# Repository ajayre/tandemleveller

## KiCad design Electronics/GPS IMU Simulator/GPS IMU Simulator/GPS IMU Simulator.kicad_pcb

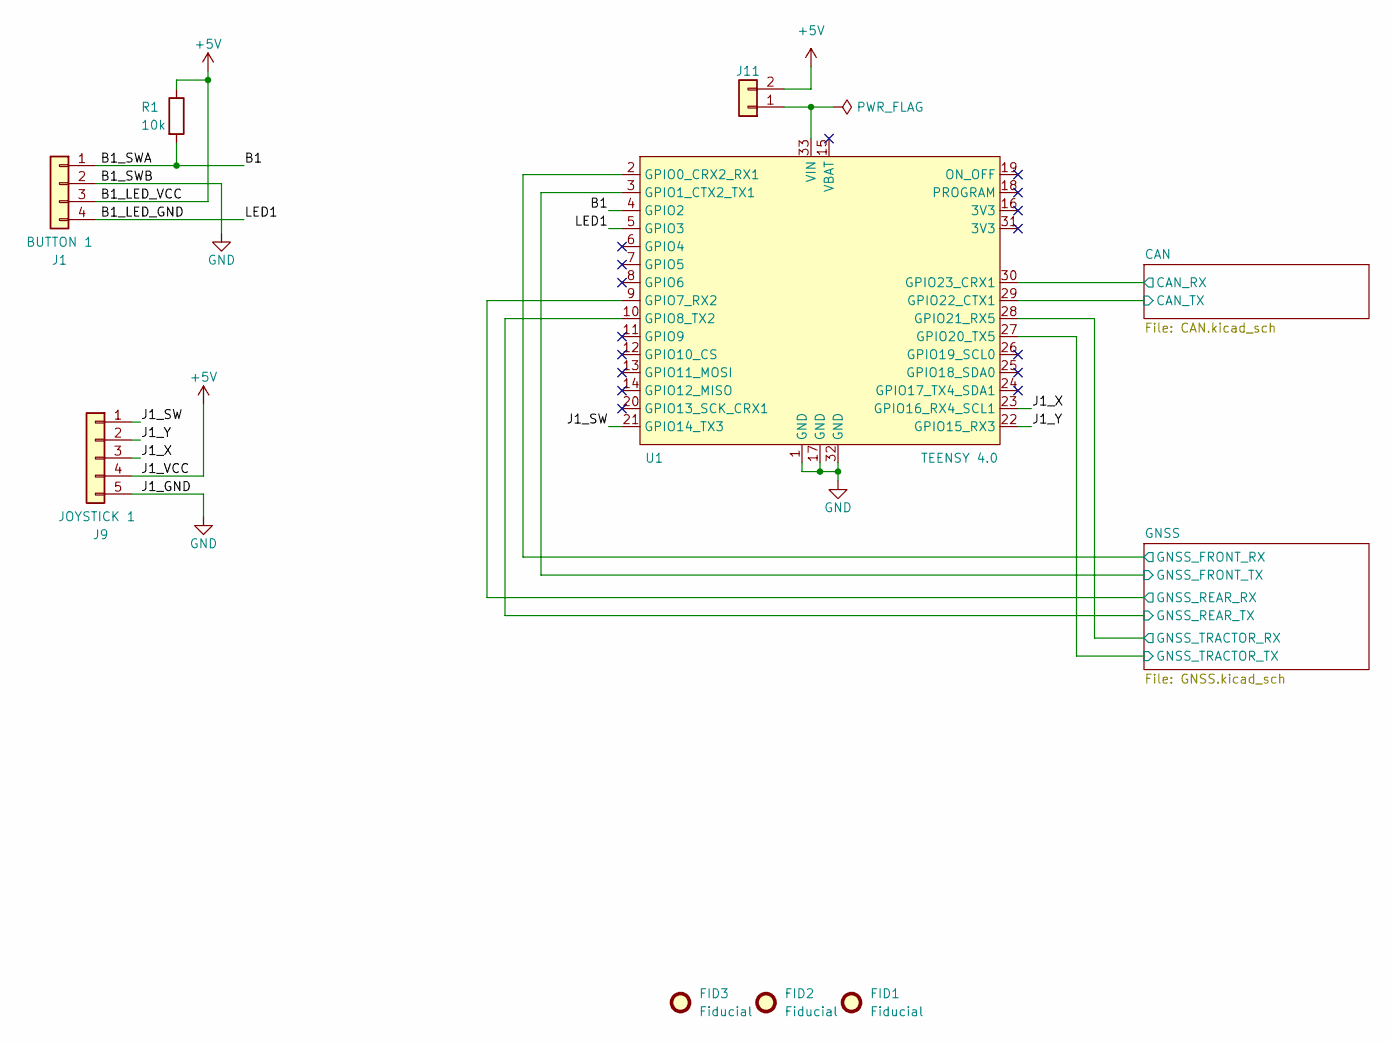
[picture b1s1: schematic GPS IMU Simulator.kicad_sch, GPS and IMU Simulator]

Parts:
FID1, FID2, FID3: Fiducial; Fiducial_0.5mm_Mask1mm
J1: BUTTON 1; JST_PH_B4B-PH-K_1x04_P2.00mm_Vertical; LCSC C131334
J9: JOYSTICK 1; JST_PH_B5B-PH-K_1x05_P2.00mm_Vertical; LCSC C157993
J11: Conn_01x02; PinHeader_1x02_P2.54mm_Vertical; LCSC C7494857
R1: 10k; R_0805_2012Metric; LCSC C17414
U1: TEENSY 4.0; Teensy_4.0

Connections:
+5V: J1.3, J9.4, J11.2, R1.1; also elsewhere on the board
/B1: J1.1, R1.2, U1.4 (GPIO2)
/B1_LED_GND: J1.4, U1.5 (GPIO3)
/CAN/CAN_RX: U1.30 (GPIO23_CRX1); also elsewhere on the board
/CAN/CAN_TX: U1.29 (GPIO22_CTX1); also elsewhere on the board
/GNSS/GNSS_FRONT_RX: U1.2 (GPIO0_CRX2_RX1); also elsewhere on the board
/GNSS/GNSS_FRONT_TX: U1.3 (GPIO1_CTX2_TX1); also elsewhere on the board
/GNSS/GNSS_REAR_RX: U1.9 (GPIO7_RX2); also elsewhere on the board
/GNSS/GNSS_REAR_TX: U1.10 (GPIO8_TX2); also elsewhere on the board
/GNSS/GNSS_TRACTOR_RX: U1.28 (GPIO21_RX5); also elsewhere on the board
/GNSS/GNSS_TRACTOR_TX: U1.27 (GPIO20_TX5); also elsewhere on the board
/J1_SW: J9.1, U1.21 (GPIO14_TX3)
/J1_X: J9.3, U1.23 (GPIO16_RX4_SCL1)
/J1_Y: J9.2, U1.22 (GPIO15_RX3)
GND: J1.2, J9.5, U1.1 (GND), U1.17 (GND), U1.32 (GND); also elsewhere on the board
unnamed: J11.1, U1.33 (VIN)

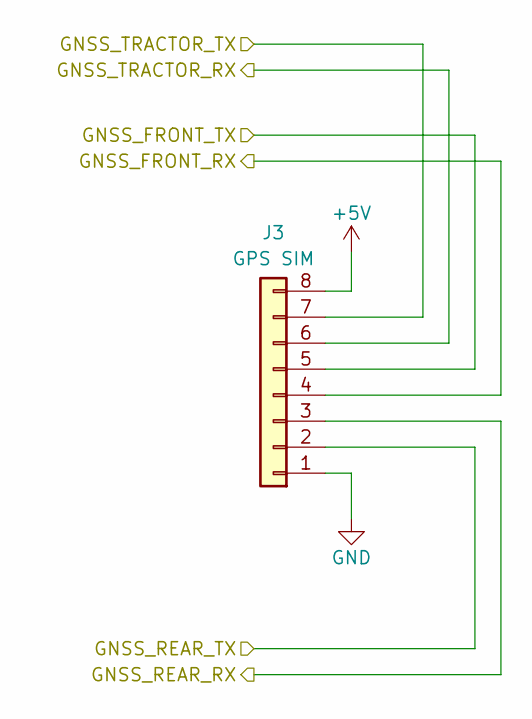
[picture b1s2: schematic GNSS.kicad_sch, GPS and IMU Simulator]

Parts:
J3: GPS SIM; JST_PH_B8B-PH-K_1x08_P2.00mm_Vertical; LCSC C157974

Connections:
+5V: J3.8; also elsewhere on the board
/GNSS/GNSS_FRONT_RX: J3.4; also elsewhere on the board
/GNSS/GNSS_FRONT_TX: J3.5; also elsewhere on the board
/GNSS/GNSS_REAR_RX: J3.3; also elsewhere on the board
/GNSS/GNSS_REAR_TX: J3.2; also elsewhere on the board
/GNSS/GNSS_TRACTOR_RX: J3.6; also elsewhere on the board
/GNSS/GNSS_TRACTOR_TX: J3.7; also elsewhere on the board
GND: J3.1; also elsewhere on the board

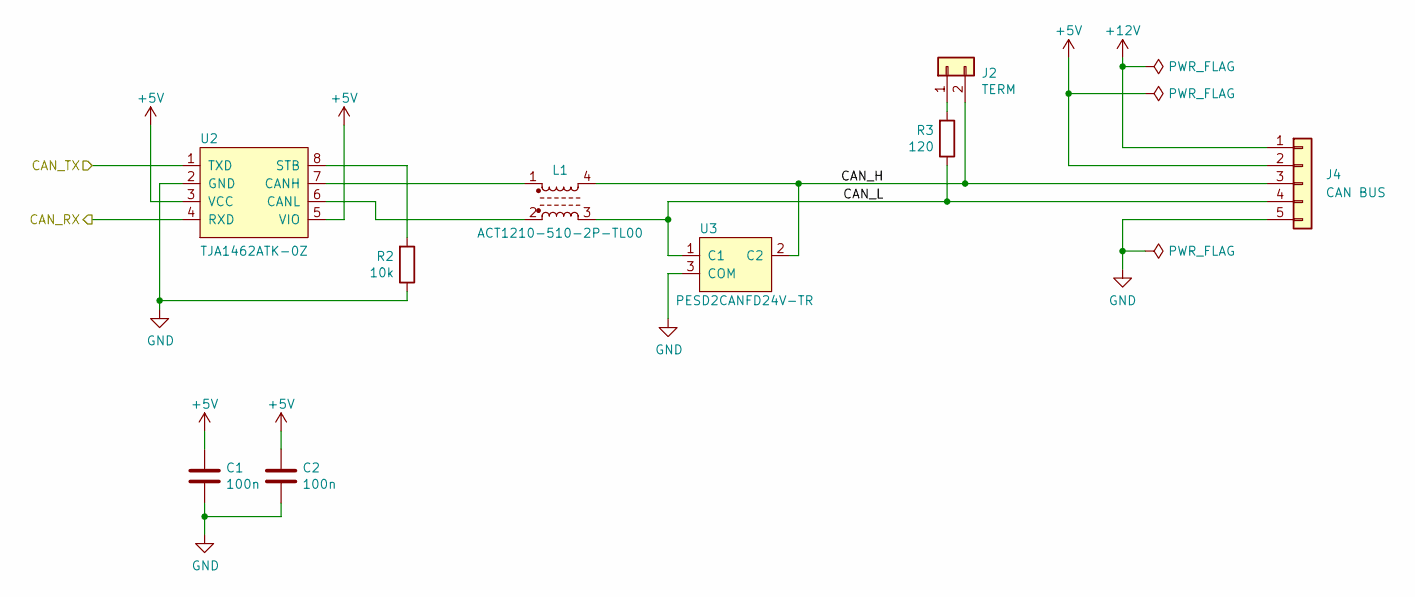
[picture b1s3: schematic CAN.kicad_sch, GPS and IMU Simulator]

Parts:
C1, C2: 100n; C_0805_2012Metric; LCSC C1711
J2: TERM; PinHeader_1x02_P2.54mm_Vertical; LCSC C7494857
J4: CAN BUS; JST_PH_B5B-PH-K_1x05_P2.00mm_Vertical; LCSC C157993
L1: ACT1210-510-2P-TL00; LCSC C95572
R2: 10k; R_0805_2012Metric; LCSC C17414
R3: 120; R_0805_2012Metric; LCSC C17437
U2: TJA1462ATK-0Z; HVSON8_0_65mm; LCSC C3229259
U3: PESD2CANFD24V-TR; SOT-23; LCSC C552486

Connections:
+5V: C1.1, C2.1, J4.2, U2.3 (VCC), U2.5 (VIO); also elsewhere on the board
+12V: J4.1
/CAN/CAN_H: J2.2, J4.3, L1.4, U3.2 (C2)
/CAN/CAN_L: J4.4, L1.3, R3.1, U3.1 (C1)
/CAN/CAN_RX: U2.4 (RXD); also elsewhere on the board
/CAN/CAN_TX: U2.1 (TXD); also elsewhere on the board
GND: C1.2, C2.2, J4.5, R2.1, U2.2 (GND), U3.3 (COM); also elsewhere on the board
unnamed: J2.1, R3.2
unnamed: L1.1, U2.7 (CANH)
unnamed: L1.2, U2.6 (CANL)
unnamed: R2.2, U2.8 (STB)

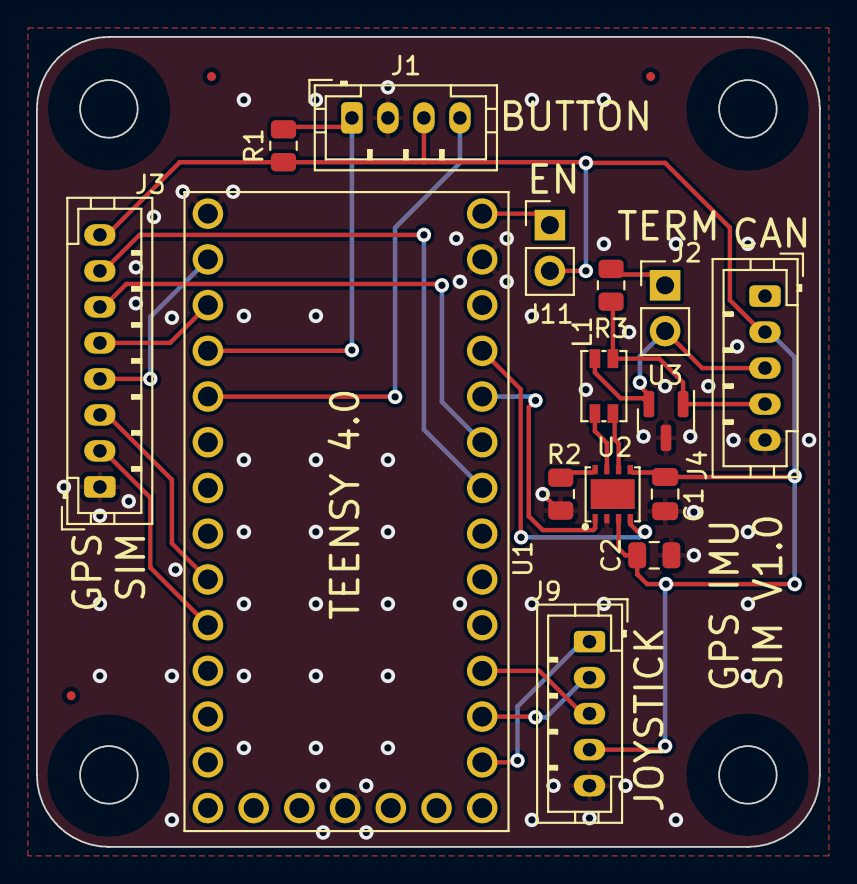
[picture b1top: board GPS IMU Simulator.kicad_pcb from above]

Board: 2 copper layers, 43.5 x 45.0 mm, 18 parts (0 on the bottom side), 22 nets.

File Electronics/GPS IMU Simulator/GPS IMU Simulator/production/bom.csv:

Designator,Footprint,Quantity,Value,LCSC Part #
"C1, C2",0805,2,100n,C1711
"FID1, FID2, FID3",Fiducial_0.5mm_Mask1mm,3,Fiducial,
J1,JST_PH_B4B-PH-K_1x04_P2.00mm_Vertical,1,BUTTON 1,C131334
J11,PinHeader_1x02_P2.54mm_Vertical,1,Conn_01x02,C7494857
J2,PinHeader_1x02_P2.54mm_Vertical,1,TERM,C7494857
J3,JST_PH_B8B-PH-K_1x08_P2.00mm_Vertical,1,GPS SIM,C157974
J4,JST_PH_B5B-PH-K_1x05_P2.00mm_Vertical,1,CAN BUS,C157993
J9,JST_PH_B5B-PH-K_1x05_P2.00mm_Vertical,1,JOYSTICK 1,C157993
L1,ACT1210-510-2P-TL00,1,ACT1210-510-2P-TL00,C95572
"R1, R2",0805,2,10k,C17414
R3,0805,1,120,C17437
U1,Teensy_4.0,1,TEENSY 4.0,
U2,HVSON8_0_65mm,1,TJA1462ATK-0Z,C3229259
U3,SOT-23,1,PESD2CANFD24V-TR,C552486

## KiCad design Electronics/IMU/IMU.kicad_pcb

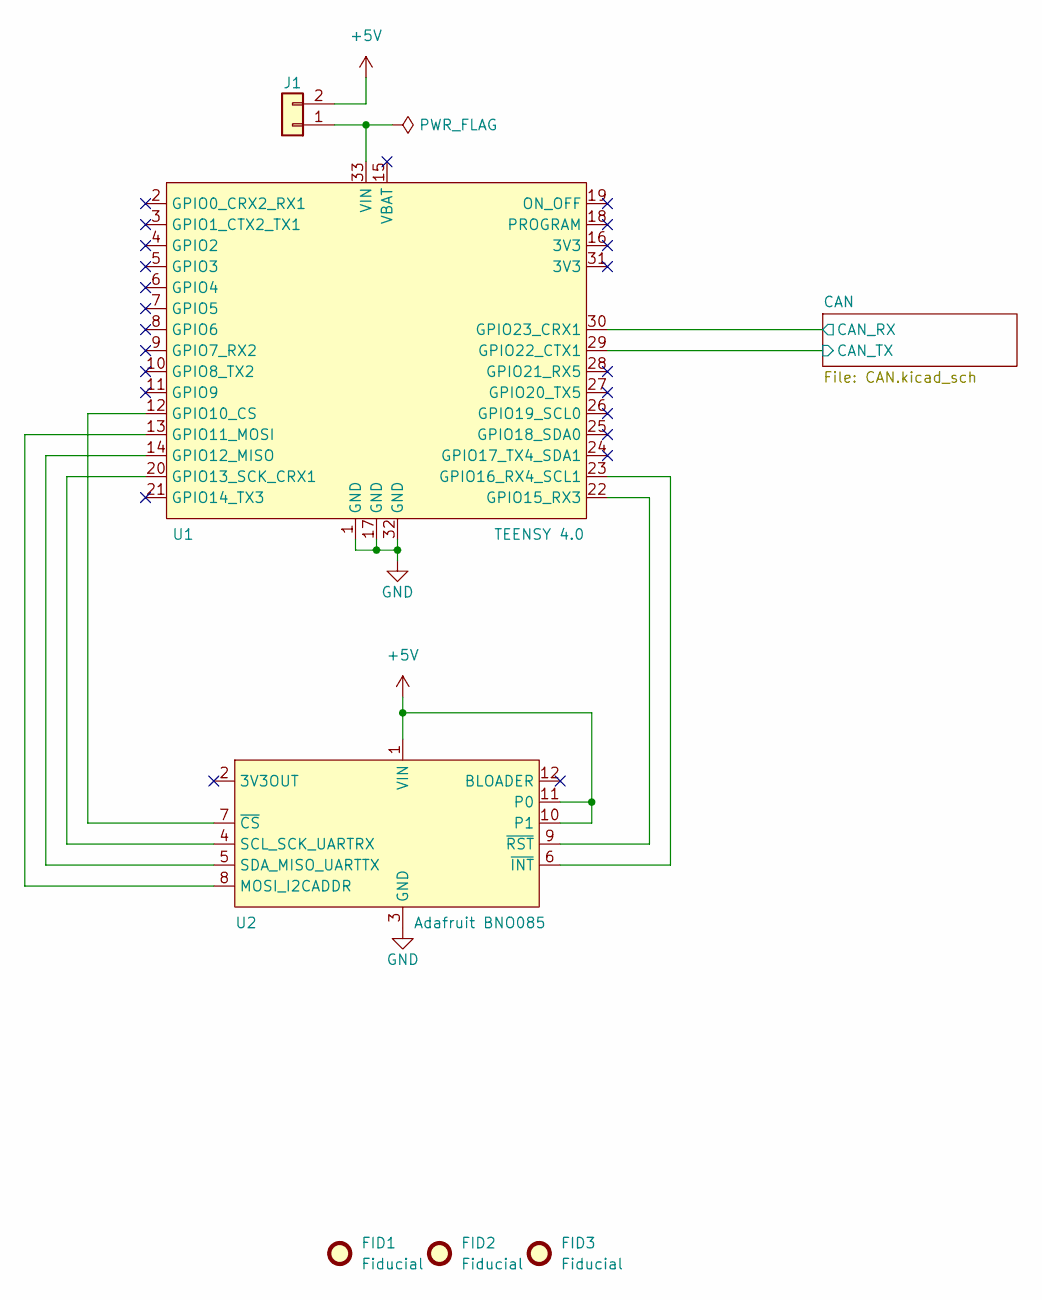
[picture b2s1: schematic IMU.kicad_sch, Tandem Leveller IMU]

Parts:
FID1, FID2, FID3: Fiducial; Fiducial_0.5mm_Mask1mm
J1: Conn_01x02; PinHeader_1x02_P2.54mm_Vertical; LCSC C7494857
U1: TEENSY 4.0; Teensy_4.0
U2: Adafruit BNO085; Adafruit_BNO085

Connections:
+5V: J1.2, U2.1 (VIN), U2.10 (P1), U2.11 (P0); also elsewhere on the board
/CAN/CAN_RX: U1.30 (GPIO23_CRX1); also elsewhere on the board
/CAN/CAN_TX: U1.29 (GPIO22_CTX1); also elsewhere on the board
GND: U1.1 (GND), U1.17 (GND), U1.32 (GND), U2.3 (GND); also elsewhere on the board
unnamed: J1.1, U1.33 (VIN)
unnamed: U1.12 (GPIO10_CS), U2.7 (~CS)
unnamed: U1.13 (GPIO11_MOSI), U2.8 (MOSI_I2CADDR)
unnamed: U1.14 (GPIO12_MISO), U2.5 (SDA_MISO_UARTTX)
unnamed: U1.20 (GPIO13_SCK_CRX1), U2.4 (SCL_SCK_UARTRX)
unnamed: U1.22 (GPIO15_RX3), U2.9 (~RST)
unnamed: U1.23 (GPIO16_RX4_SCL1), U2.6 (~INT)

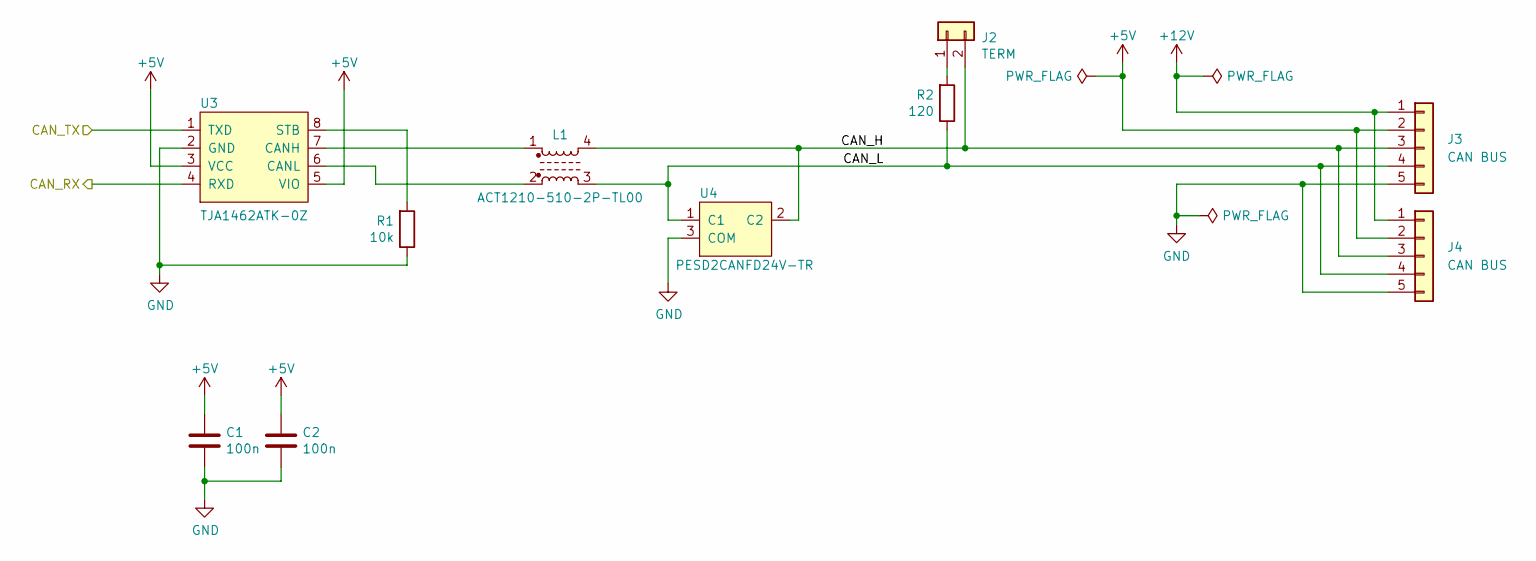
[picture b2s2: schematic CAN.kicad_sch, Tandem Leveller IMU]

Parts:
C1, C2: 100n; C_0805_2012Metric; LCSC C1711
J2: TERM; PinHeader_1x02_P2.54mm_Vertical; LCSC C7494857
J3, J4: CAN BUS; JST_PH_B5B-PH-K_1x05_P2.00mm_Vertical; LCSC C157993
L1: ACT1210-510-2P-TL00; LCSC C95572
R1: 10k; R_0805_2012Metric; LCSC C17414
R2: 120; R_0805_2012Metric; LCSC C17437
U3: TJA1462ATK-0Z; HVSON8_0_65mm; LCSC C3229259
U4: PESD2CANFD24V-TR; SOT-23; LCSC C552486

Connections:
+5V: C1.1, C2.1, J3.2, J4.2, U3.3 (VCC), U3.5 (VIO); also elsewhere on the board
+12V: J3.1, J4.1
/CAN/CAN_H: J2.2, J3.3, J4.3, L1.4, U4.2 (C2)
/CAN/CAN_L: J3.4, J4.4, L1.3, R2.1, U4.1 (C1)
/CAN/CAN_RX: U3.4 (RXD); also elsewhere on the board
/CAN/CAN_TX: U3.1 (TXD); also elsewhere on the board
GND: C1.2, C2.2, J3.5, J4.5, R1.1, U3.2 (GND), U4.3 (COM); also elsewhere on the board
unnamed: J2.1, R2.2
unnamed: L1.1, U3.7 (CANH)
unnamed: L1.2, U3.6 (CANL)
unnamed: R1.2, U3.8 (STB)

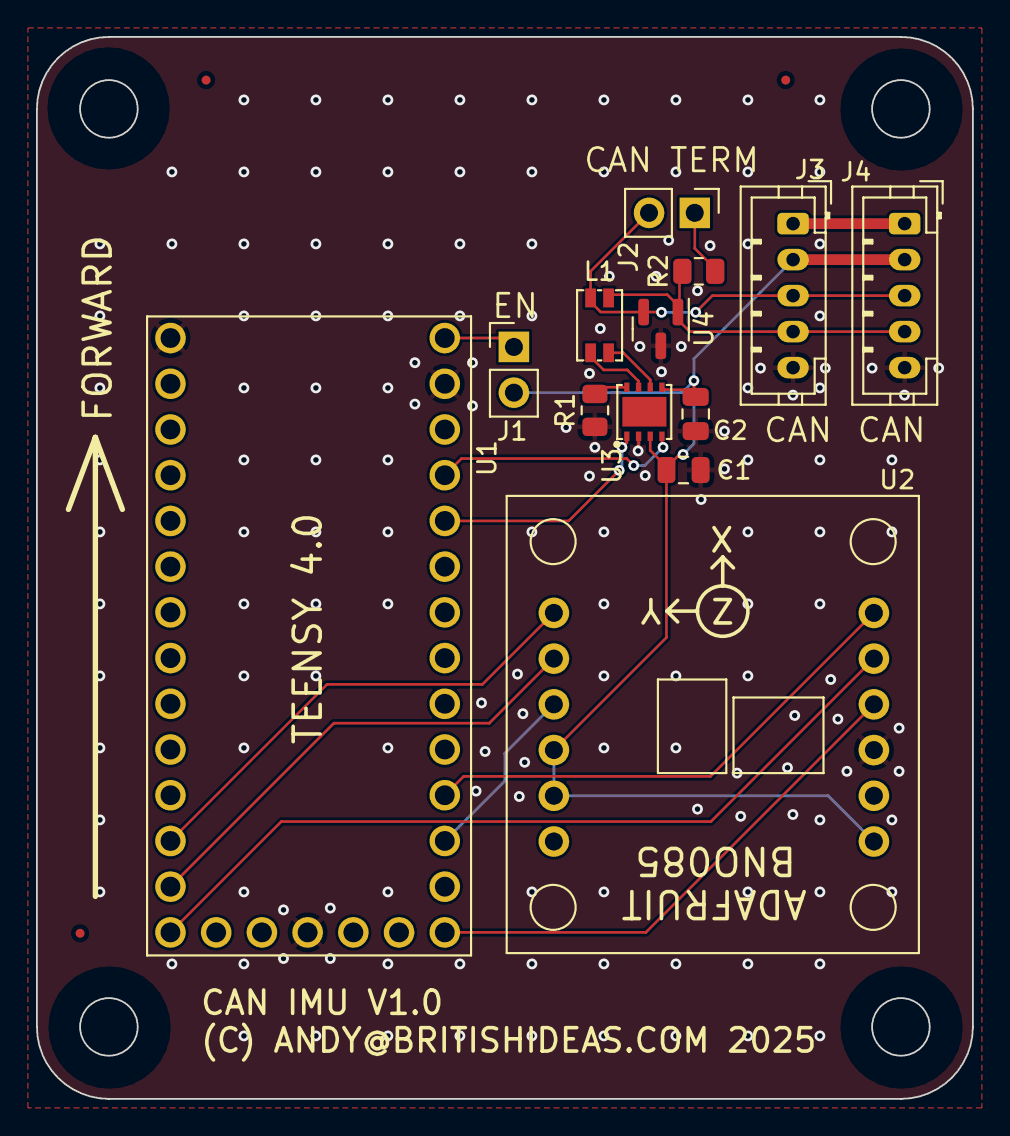
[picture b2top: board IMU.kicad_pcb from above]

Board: 2 copper layers, 52.0 x 59.0 mm, 16 parts (0 on the bottom side), 18 nets.

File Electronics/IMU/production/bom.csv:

Designator,Footprint,Quantity,Value,LCSC Part #
"C1, C2",0805,2,100n,C1711
"FID1, FID2, FID3",Fiducial_0.5mm_Mask1mm,3,Fiducial,
J1,PinHeader_1x02_P2.54mm_Vertical,1,Conn_01x02,C7494857
J2,PinHeader_1x02_P2.54mm_Vertical,1,TERM,C7494857
"J3, J4",JST_PH_B5B-PH-K_1x05_P2.00mm_Vertical,2,CAN BUS,C157993
L1,ACT1210-510-2P-TL00,1,ACT1210-510-2P-TL00,C95572
R1,0805,1,10k,C17414
R2,0805,1,120,C17437
U1,Teensy_4.0,1,TEENSY 4.0,
U2,Adafruit_BNO085,1,Adafruit BNO085,
U3,HVSON8_0_65mm,1,TJA1462ATK-0Z,C3229259
U4,SOT-23,1,PESD2CANFD24V-TR,C552486

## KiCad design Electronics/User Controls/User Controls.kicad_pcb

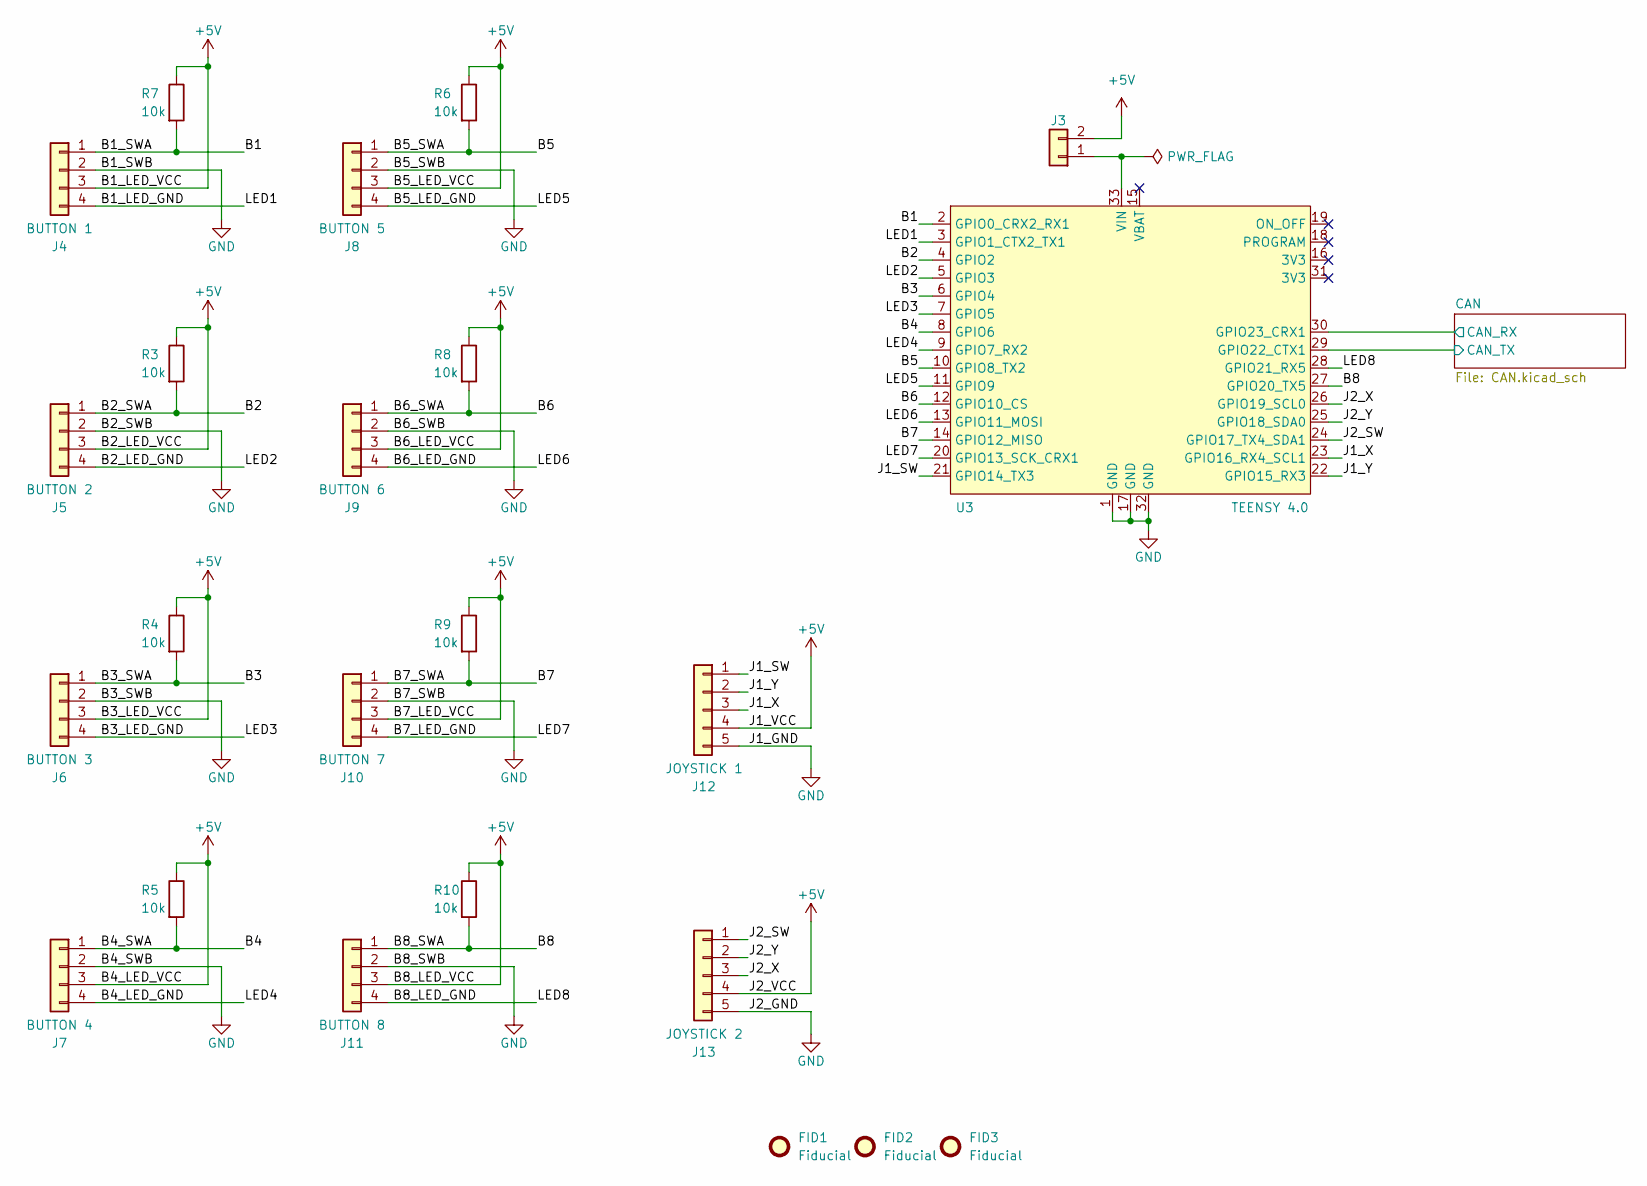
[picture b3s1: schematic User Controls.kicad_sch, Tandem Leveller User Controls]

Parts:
FID1, FID2, FID3: Fiducial; Fiducial_0.5mm_Mask1mm
J3: Conn_01x02; PinHeader_1x02_P2.54mm_Vertical; LCSC C7494857
J4: BUTTON 1; JST_PH_B4B-PH-K_1x04_P2.00mm_Vertical; LCSC C131334
J5: BUTTON 2; JST_PH_B4B-PH-K_1x04_P2.00mm_Vertical; LCSC C131334
J6: BUTTON 3; JST_PH_B4B-PH-K_1x04_P2.00mm_Vertical; LCSC C131334
J7: BUTTON 4; JST_PH_B4B-PH-K_1x04_P2.00mm_Vertical; LCSC C131334
J8: BUTTON 5; JST_PH_B4B-PH-K_1x04_P2.00mm_Vertical; LCSC C131334
J9: BUTTON 6; JST_PH_B4B-PH-K_1x04_P2.00mm_Vertical; LCSC C131334
J10: BUTTON 7; JST_PH_B4B-PH-K_1x04_P2.00mm_Vertical; LCSC C131334
J11: BUTTON 8; JST_PH_B4B-PH-K_1x04_P2.00mm_Vertical; LCSC C131334
J12: JOYSTICK 1; JST_PH_B5B-PH-K_1x05_P2.00mm_Vertical; LCSC C157993
J13: JOYSTICK 2; JST_PH_B5B-PH-K_1x05_P2.00mm_Vertical; LCSC C157993
R3, R4, R5, R6, R7, R8, R9, R10: 10k; R_0805_2012Metric; LCSC C17414
U3: TEENSY 4.0; Teensy_4.0

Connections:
+5V: J3.2, J4.3, J5.3, J6.3, J7.3, J8.3, J9.3, J10.3, J11.3, J12.4, J13.4, R3.1, R4.1, R5.1, R6.1, R7.1, R8.1, R9.1, R10.1; also elsewhere on the board
/B1: J4.1, R7.2, U3.2 (GPIO0_CRX2_RX1)
/B1_LED_GND: J4.4, U3.3 (GPIO1_CTX2_TX1)
/B2: J5.1, R3.2, U3.4 (GPIO2)
/B2_LED_GND: J5.4, U3.5 (GPIO3)
/B3: J6.1, R4.2, U3.6 (GPIO4)
/B3_LED_GND: J6.4, U3.7 (GPIO5)
/B4: J7.1, R5.2, U3.8 (GPIO6)
/B4_LED_GND: J7.4, U3.9 (GPIO7_RX2)
/B5: J8.1, R6.2, U3.10 (GPIO8_TX2)
/B5_LED_GND: J8.4, U3.11 (GPIO9)
/B6: J9.1, R8.2, U3.12 (GPIO10_CS)
/B6_LED_GND: J9.4, U3.13 (GPIO11_MOSI)
/B7: J10.1, R9.2, U3.14 (GPIO12_MISO)
/B7_LED_GND: J10.4, U3.20 (GPIO13_SCK_CRX1)
/B8: J11.1, R10.2, U3.27 (GPIO20_TX5)
/B8_LED_GND: J11.4, U3.28 (GPIO21_RX5)
/CAN/CAN_RX: U3.30 (GPIO23_CRX1); also elsewhere on the board
/CAN/CAN_TX: U3.29 (GPIO22_CTX1); also elsewhere on the board
/J1_SW: J12.1, U3.21 (GPIO14_TX3)
/J1_X: J12.3, U3.23 (GPIO16_RX4_SCL1)
/J1_Y: J12.2, U3.22 (GPIO15_RX3)
/J2_SW: J13.1, U3.24 (GPIO17_TX4_SDA1)
/J2_X: J13.3, U3.26 (GPIO19_SCL0)
/J2_Y: J13.2, U3.25 (GPIO18_SDA0)
GND: J4.2, J5.2, J6.2, J7.2, J8.2, J9.2, J10.2, J11.2, J12.5, J13.5, U3.1 (GND), U3.17 (GND), U3.32 (GND); also elsewhere on the board
unnamed: J3.1, U3.33 (VIN)

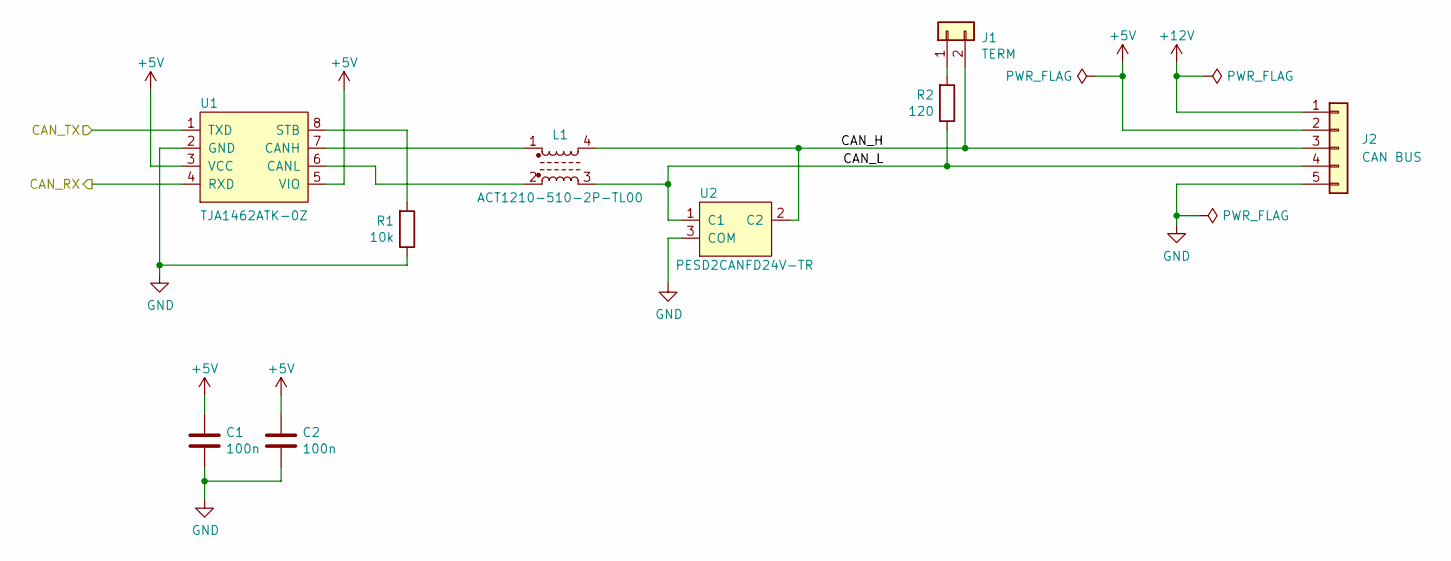
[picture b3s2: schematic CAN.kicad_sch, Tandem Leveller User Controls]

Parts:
C1, C2: 100n; C_0805_2012Metric; LCSC C1711
J1: TERM; PinHeader_1x02_P2.54mm_Vertical; LCSC C7494857
J2: CAN BUS; JST_PH_B5B-PH-K_1x05_P2.00mm_Vertical; LCSC C157993
L1: ACT1210-510-2P-TL00; LCSC C95572
R1: 10k; R_0805_2012Metric; LCSC C17414
R2: 120; R_0805_2012Metric; LCSC C17437
U1: TJA1462ATK-0Z; HVSON8_0_65mm; LCSC C3229259
U2: PESD2CANFD24V-TR; SOT-23; LCSC C552486

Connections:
+5V: C1.1, C2.1, J2.2, U1.3 (VCC), U1.5 (VIO); also elsewhere on the board
+12V: J2.1
/CAN/CAN_H: J1.2, J2.3, L1.4, U2.2 (C2)
/CAN/CAN_L: J2.4, L1.3, R2.1, U2.1 (C1)
/CAN/CAN_RX: U1.4 (RXD); also elsewhere on the board
/CAN/CAN_TX: U1.1 (TXD); also elsewhere on the board
GND: C1.2, C2.2, J2.5, R1.1, U1.2 (GND), U2.3 (COM); also elsewhere on the board
unnamed: J1.1, R2.2
unnamed: L1.1, U1.7 (CANH)
unnamed: L1.2, U1.6 (CANL)
unnamed: R1.2, U1.8 (STB)

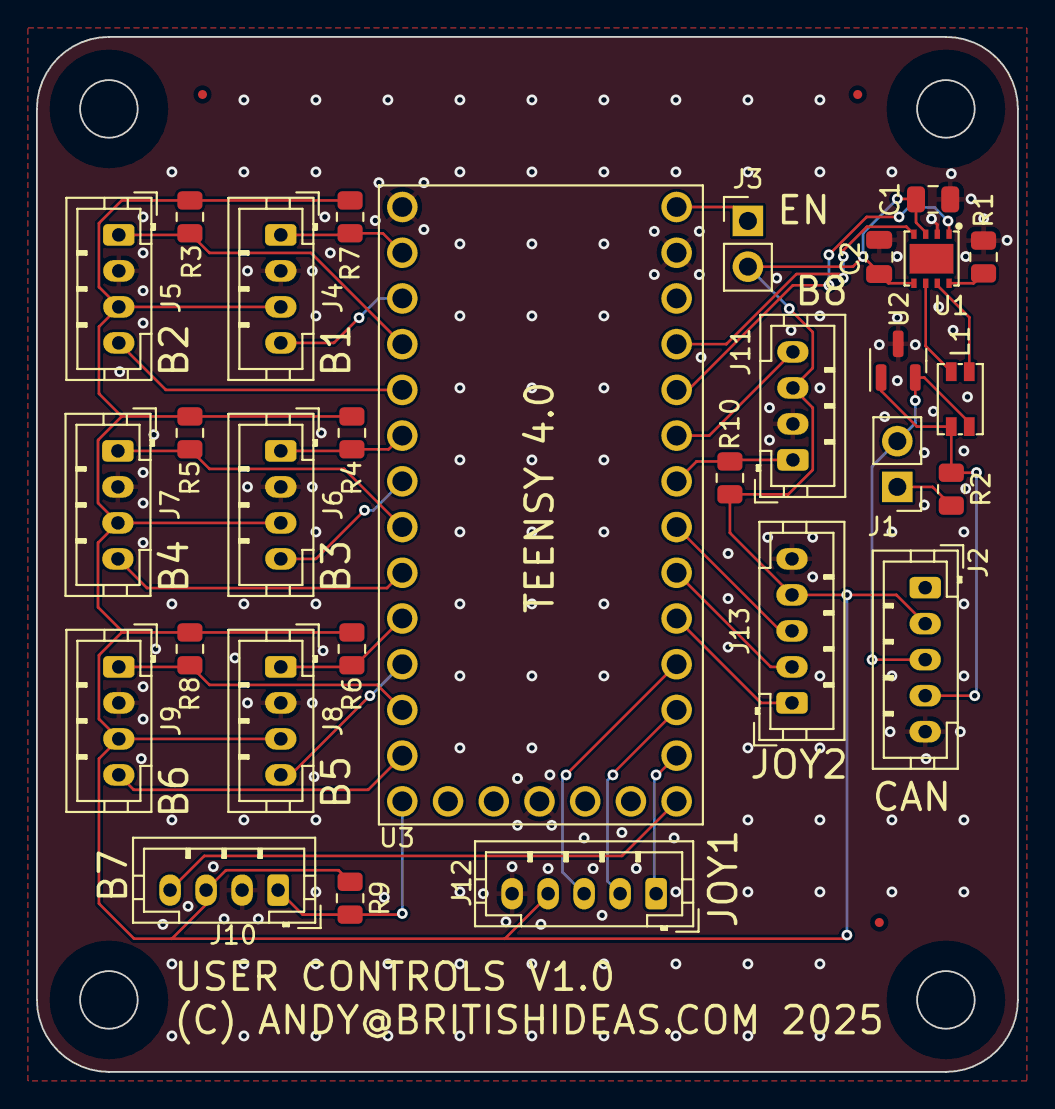
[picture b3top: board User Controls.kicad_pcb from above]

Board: 2 copper layers, 54.5 x 57.5 mm, 32 parts (0 on the bottom side), 33 nets.

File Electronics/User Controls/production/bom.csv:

Designator,Footprint,Quantity,Value,LCSC Part #
"C1, C2",0805,2,100n,C1711
"FID1, FID2, FID3",Fiducial_0.5mm_Mask1mm,3,Fiducial,
J1,PinHeader_1x02_P2.54mm_Vertical,1,TERM,C7494857
J10,JST_PH_B4B-PH-K_1x04_P2.00mm_Vertical,1,BUTTON 7,C131334
J11,JST_PH_B4B-PH-K_1x04_P2.00mm_Vertical,1,BUTTON 8,C131334
J12,JST_PH_B5B-PH-K_1x05_P2.00mm_Vertical,1,JOYSTICK 1,C157993
J13,JST_PH_B5B-PH-K_1x05_P2.00mm_Vertical,1,JOYSTICK 2,C157993
J2,JST_PH_B5B-PH-K_1x05_P2.00mm_Vertical,1,CAN BUS,C157993
J3,PinHeader_1x02_P2.54mm_Vertical,1,Conn_01x02,C7494857
J4,JST_PH_B4B-PH-K_1x04_P2.00mm_Vertical,1,BUTTON 1,C131334
J5,JST_PH_B4B-PH-K_1x04_P2.00mm_Vertical,1,BUTTON 2,C131334
J6,JST_PH_B4B-PH-K_1x04_P2.00mm_Vertical,1,BUTTON 3,C131334
J7,JST_PH_B4B-PH-K_1x04_P2.00mm_Vertical,1,BUTTON 4,C131334
J8,JST_PH_B4B-PH-K_1x04_P2.00mm_Vertical,1,BUTTON 5,C131334
J9,JST_PH_B4B-PH-K_1x04_P2.00mm_Vertical,1,BUTTON 6,C131334
L1,ACT1210-510-2P-TL00,1,ACT1210-510-2P-TL00,C95572
"R1, R10, R3, R4, R5, R6, R7, R8, R9",0805,9,10k,C17414
R2,0805,1,120,C17437
U1,HVSON8_0_65mm,1,TJA1462ATK-0Z,C3229259
U2,SOT-23,1,PESD2CANFD24V-TR,C552486
U3,Teensy_4.0,1,TEENSY 4.0,
